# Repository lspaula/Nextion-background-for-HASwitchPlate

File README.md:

# Nextion-background-for-HASwitchPlate

The HASwitchPlate developed by [@aderusha](https://github.com/aderusha/HASwitchPlate) has a blank background and I developed a picture based background to make it more attractive. There are now both the 2.4" (with the original HASP pages) and the 3.5" (with a tailored to my system set of pages) display files available. I decided to use 3.5" version of the display, which gives me more area, resulting in a better looking. For this work, I have used the [Inkscape](https://inkscape.org) software to create the button/sliders images, which are also available and can be edited and modified as required by different panel configurations.

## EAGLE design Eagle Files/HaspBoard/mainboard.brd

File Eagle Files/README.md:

# Eagle files

Here are the files for creating a board using Eagle/Flatcam/Candle

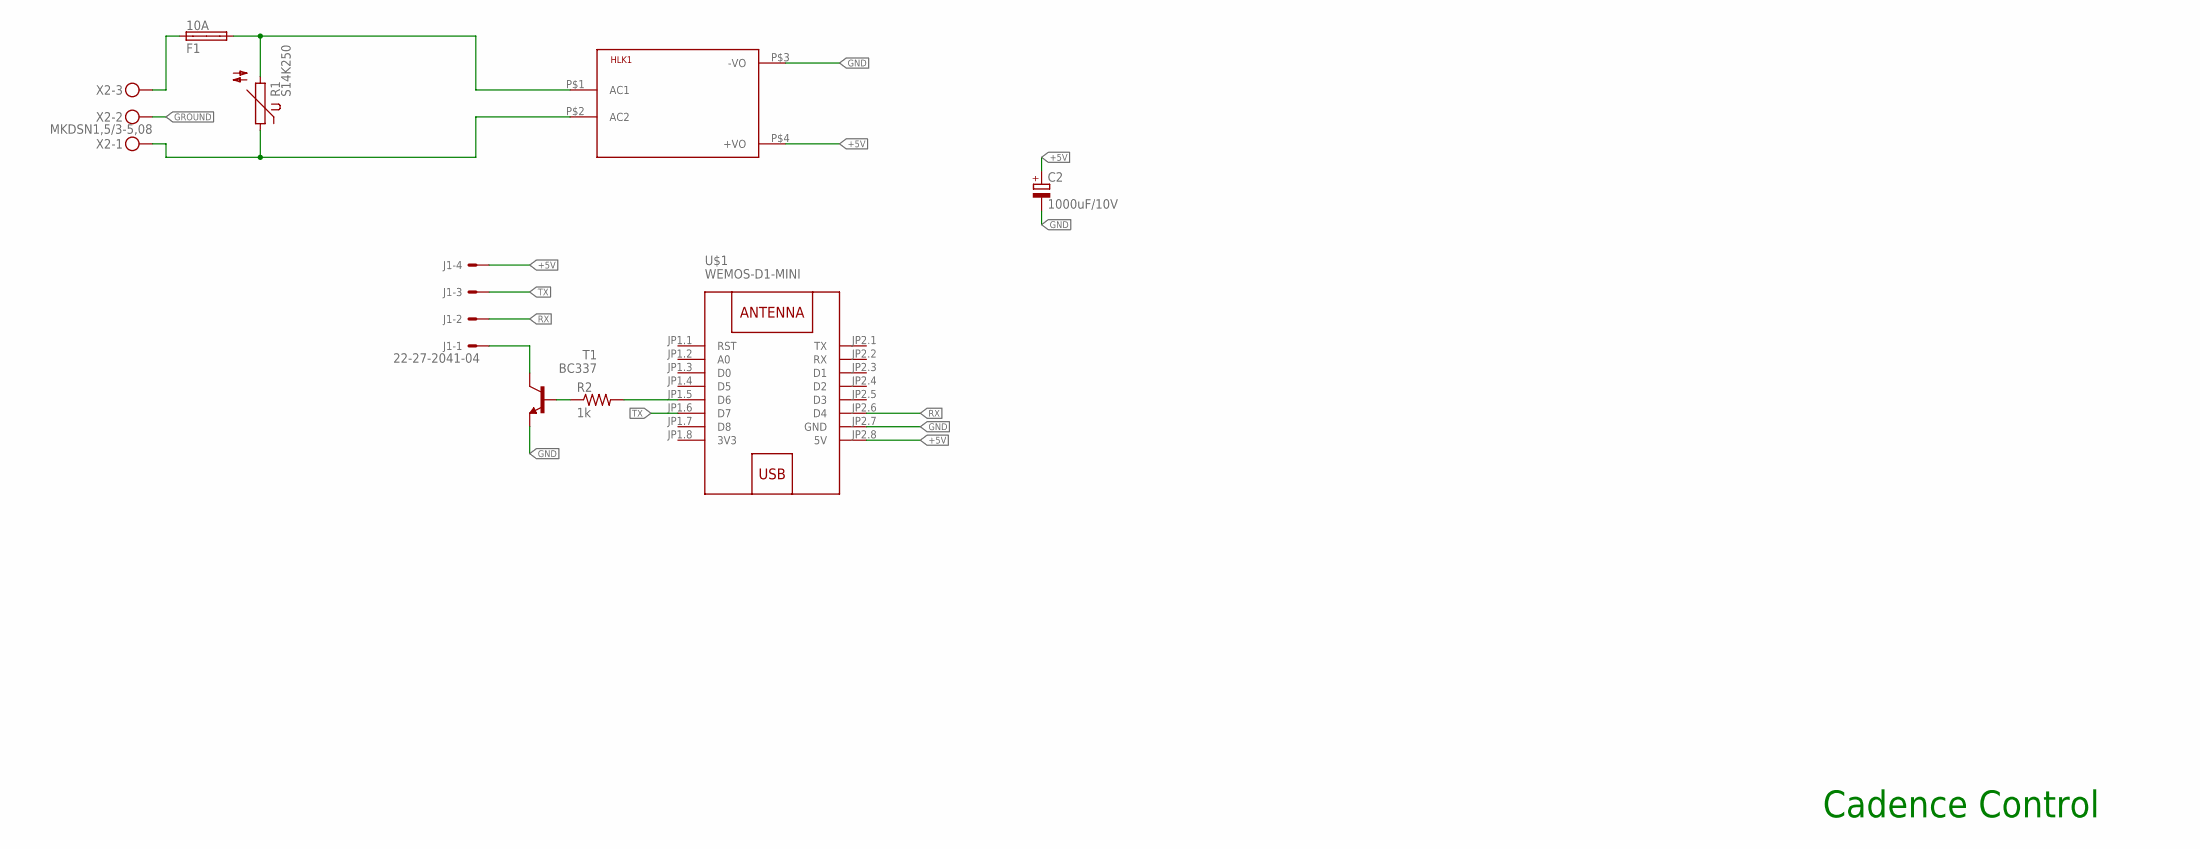
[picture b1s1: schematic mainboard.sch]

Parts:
C2: 1000uF/10V; E3,5-8
F1: 10A; SHK20L
HLK1: HLK-PM013W; HLK-PM01
J1: 22-27-2041-04; 6410-04
R1: S14K250
R2: 1k; 0207/10
T1: BC337; TO92
U$1: WEMOS-D1-MINI
X2: MKDSN1,5/3-5,08

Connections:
3V3: U$1.JP1.8 (3V3)
+5V: C2.+, HLK1.P$4 (+VO), J1.4, U$1.JP2.8 (5V)
GND: C2.-, HLK1.P$3 (-VO), T1.1 (E), U$1.JP2.7 (GND)
GROUND: X2.2
LCD_GND: J1.1, T1.3 (C)
unnamed: R2.2, U$1.JP1.5 (D6)
unnamed: R2.1, T1.2 (B)
unnamed: HLK1.P$2 (AC2), R1.1, X2.1
unnamed: F1.2A, HLK1.P$1 (AC1), R1.2
unnamed: F1.1A, X2.3
RX: J1.2, U$1.JP2.6 (D4)
TX: J1.3, U$1.JP1.6 (D7)

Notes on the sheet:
Cadence Control

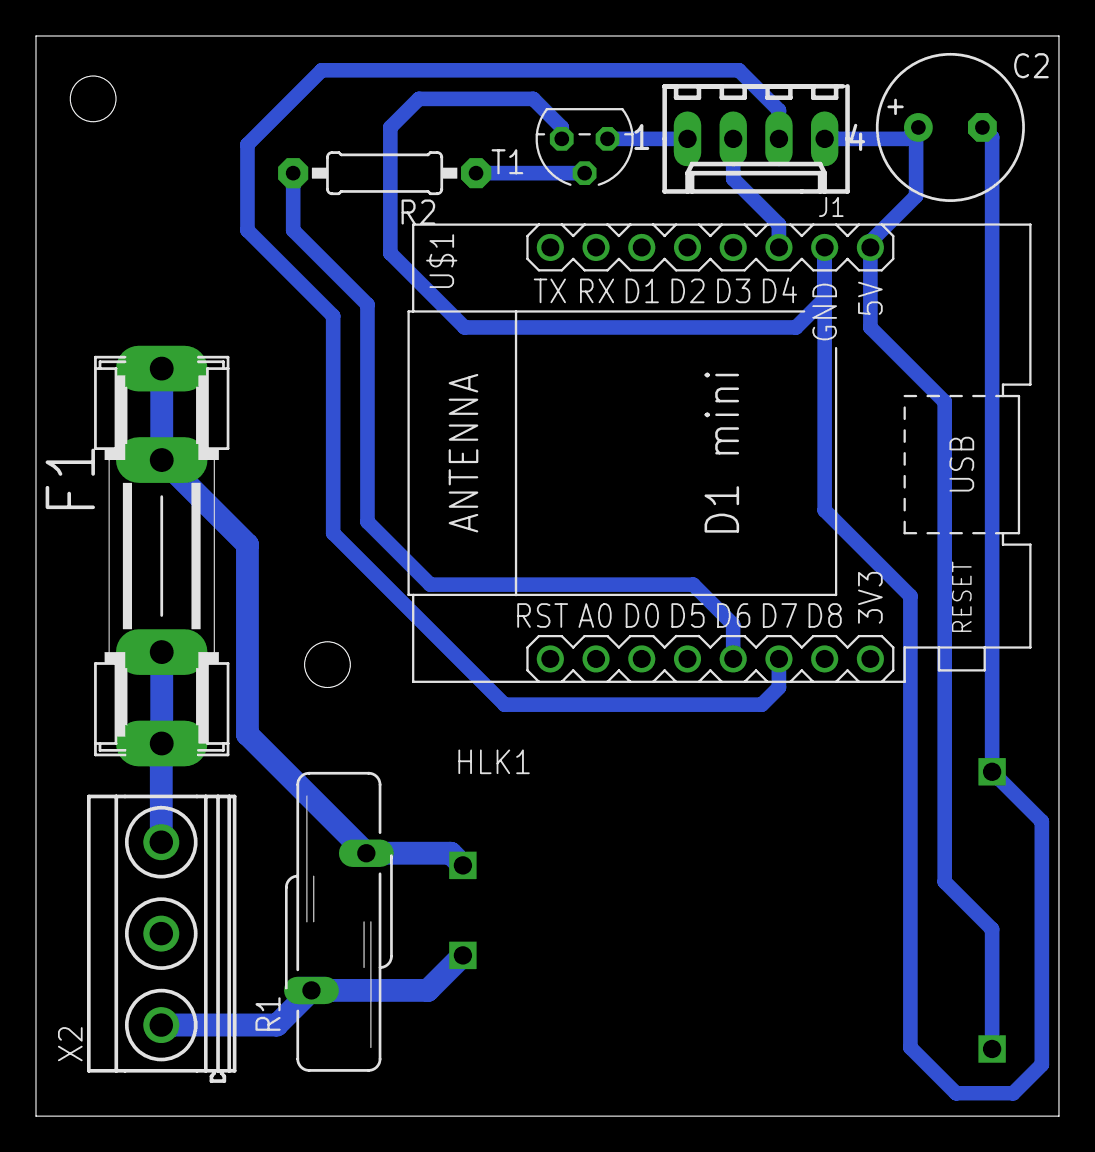
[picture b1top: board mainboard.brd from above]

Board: 2 copper layers, 56.8 x 60.0 mm, 9 parts (0 on the bottom side), 10 nets.

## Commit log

2019-09-10 Update README.md
    I have included a small description.
2019-09-11 Inclusion of all the files for the 3.5" version display
2019-09-11 All pictures and Nextion related files for the 3.5" display version have been included
2019-09-11 Removal of empty dirs
2019-09-11 Inclusion of the Openhab HaspRules file
2019-09-12 Images inclusion
2019-09-12 Removing properties from the images
2019-09-12 Resizing images
2019-09-12 Resizing image
2019-09-12 Link to aderusha included
2019-09-14 Original HASP 2.4" files have been included.
2019-09-18 Inclusion of the correct files, with the background pictures
2019-09-27 Inclusion of the HASP rules, items and sitemap.
2019-10-02 Included the String type definition to the jsonString variable.
2019-10-05 All Openhab files have been updated to run with MQTT v2
2019-10-05 First version of the Things file
2019-10-15 Led places have been moved not to overlay with the temperature values
2019-10-30 Inclusion of the single side Eagle files
2019-10-30 Inclusion of the board pictures
2019-10-30 Readme for Eagle files.
2021-05-18 Minor text changes

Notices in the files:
parts and their libraries:
diy-modules: Released under the Creative Commons Attribution 4.0 International License: http://creativecommons.org/licenses/by/4.0
